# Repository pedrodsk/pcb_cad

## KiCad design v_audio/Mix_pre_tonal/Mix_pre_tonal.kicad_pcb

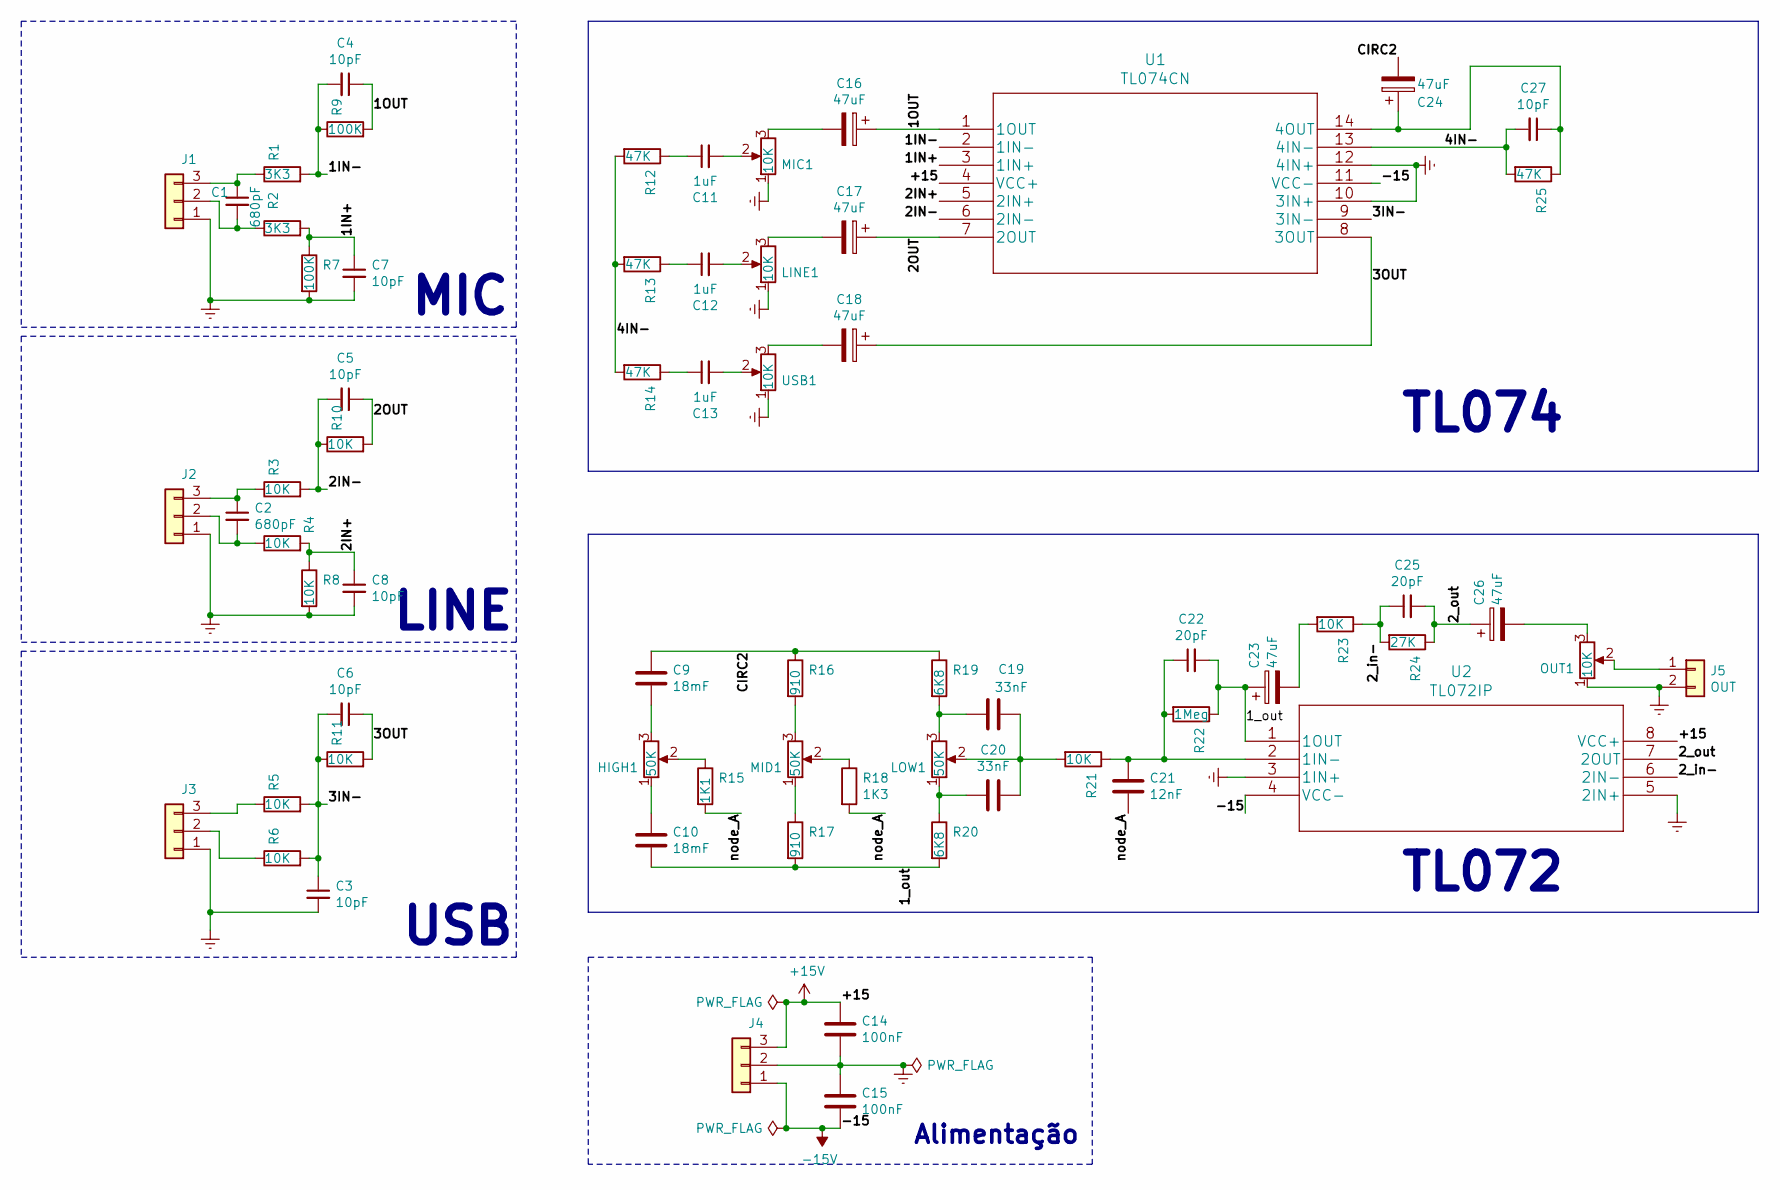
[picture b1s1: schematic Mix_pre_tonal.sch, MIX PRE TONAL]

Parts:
C1, C2: 680pF; C_Disc_D3.0mm_W1.6mm_P2.50mm
C3, C4, C5, C6, C7, C8, C27: 10pF; C_Disc_D3.0mm_W1.6mm_P2.50mm
C9, C10: 18mF; C_Disc_D7.0mm_W2.5mm_P5.00mm
C11, C12, C13: 1uF; C_Disc_D3.0mm_W1.6mm_P2.50mm
C14, C15: 100nF; C_Disc_D7.0mm_W2.5mm_P5.00mm
C16, C17, C18, C23, C24, C26: 47uF; CP_Radial_D4.0mm_P1.50mm
C19, C20: 33nF; C_Disc_D7.0mm_W2.5mm_P5.00mm
C21: 12nF; C_Disc_D7.0mm_W2.5mm_P5.00mm
C22, C25: 20pF; C_Disc_D3.0mm_W1.6mm_P2.50mm
HIGH1: 50K; Pot
J1: MIC; JST_NV_B03P-NV_1x03_P5.00mm_Vertical
J2: LINE; JST_NV_B03P-NV_1x03_P5.00mm_Vertical
J3: USB; JST_NV_B03P-NV_1x03_P5.00mm_Vertical
J4: Alimentação; JST_NV_B03P-NV_1x03_P5.00mm_Vertical
J5: OUT; JST_NV_B02P-NV_1x02_P5.00mm_Vertical
LINE1: 10K; Pot
LOW1: 50K; Pot
MIC1: 10K; Pot
MID1: 50K; Pot
OUT1: 10K; Pot
R1, R2: 3K3; R_Axial_DIN0207_L6.3mm_D2.5mm_P7.62mm_Horizontal
R3, R4, R5, R6, R8, R10, R11, R21, R23: 10K; R_Axial_DIN0207_L6.3mm_D2.5mm_P7.62mm_Horizontal
R7, R9: 100K; R_Axial_DIN0207_L6.3mm_D2.5mm_P7.62mm_Horizontal
R12, R13, R14, R25: 47K; R_Axial_DIN0207_L6.3mm_D2.5mm_P7.62mm_Horizontal
R15: 1K1; R_Axial_DIN0207_L6.3mm_D2.5mm_P7.62mm_Horizontal
R16, R17: 910; R_Axial_DIN0207_L6.3mm_D2.5mm_P7.62mm_Horizontal
R18: 1K3; R_Axial_DIN0207_L6.3mm_D2.5mm_P7.62mm_Horizontal
R19, R20: 6K8; R_Axial_DIN0207_L6.3mm_D2.5mm_P7.62mm_Horizontal
R22: 1Meg; R_Axial_DIN0207_L6.3mm_D2.5mm_P7.62mm_Horizontal
R24: 27K; R_Axial_DIN0207_L6.3mm_D2.5mm_P7.62mm_Horizontal
U1: TL074CN
U2: TL072IP
USB1: 10K; Pot

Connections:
+15V: C14.1, J4.3, U1.4 (VCC+), U2.8 (VCC+)
-15V: C15.2, J4.1, U1.11 (VCC-), U2.4 (VCC-)
/1IN+: C7.1, R2.2, R7.1, U1.3 (1IN+)
/1IN-: C4.2, R1.2, R9.1, U1.2 (1IN-)
/1OUT: C4.1, C16.1, R9.2, U1.1 (1OUT)
/1_out: C10.2, C22.2, C23.1, R17.2, R20.2, R22.1, U2.1 (1OUT)
/2IN+: C8.1, R4.2, R8.1, U1.5 (2IN+)
/2IN-: C5.2, R3.2, R10.1, U1.6 (2IN-)
/2OUT: C5.1, C17.1, R10.2, U1.7 (2OUT)
/2_in-: C25.1, R23.1, R24.2, U2.6 (2IN-)
/2_out: C25.2, C26.1, R24.1, U2.7 (2OUT)
/3IN-: C3.1, C6.2, R5.2, R6.2, R11.1, U1.9 (3IN-)
/3OUT: C6.1, C18.1, R11.2, U1.8 (3OUT)
/4IN-: C27.2, R12.2, R13.2, R14.2, R25.2, U1.13 (4IN-)
/CIRC2: C9.1, C24.2, R16.1, R19.1
/node_A: C21.1, R15.2, R18.2
GNDREF: C3.2, C7.2, C8.2, C14.2, C15.1, J1.1, J2.1, J3.1, J4.2, J5.2, LINE1.1, MIC1.1, OUT1.1, R7.2, R8.2, U1.10 (3IN+), U1.12 (4IN+), U2.3 (1IN+), U2.5 (2IN+), USB1.1
unnamed: C1.1, J1.3, R1.1
unnamed: C1.2, J1.2, R2.1
unnamed: C2.1, J2.3, R3.1
unnamed: C2.2, J2.2, R4.1
unnamed: C9.2, HIGH1.3
unnamed: C10.1, HIGH1.1
unnamed: C11.1, R12.1
unnamed: C11.2, MIC1.2
unnamed: C12.1, R13.1
unnamed: C12.2, LINE1.2
unnamed: C13.1, R14.1
unnamed: C13.2, USB1.2
unnamed: C16.2, MIC1.3
unnamed: C17.2, LINE1.3
unnamed: C18.2, USB1.3
unnamed: C19.1, C20.1, LOW1.2, R21.2
unnamed: C19.2, LOW1.3, R19.2
unnamed: C20.2, LOW1.1, R20.1
unnamed: C21.2, C22.1, R21.1, R22.2, U2.2 (1IN-)
unnamed: C23.2, R23.2
unnamed: C24.1, C27.1, R25.1, U1.14 (4OUT)
unnamed: C26.2, OUT1.3
unnamed: HIGH1.2, R15.1
unnamed: J3.2, R6.1
unnamed: J3.3, R5.1
unnamed: J5.1, OUT1.2
unnamed: MID1.1, R17.1
unnamed: MID1.2, R18.1
unnamed: MID1.3, R16.2

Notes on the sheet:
MIC
LINE
USB
TL074
TL072
Alimentação

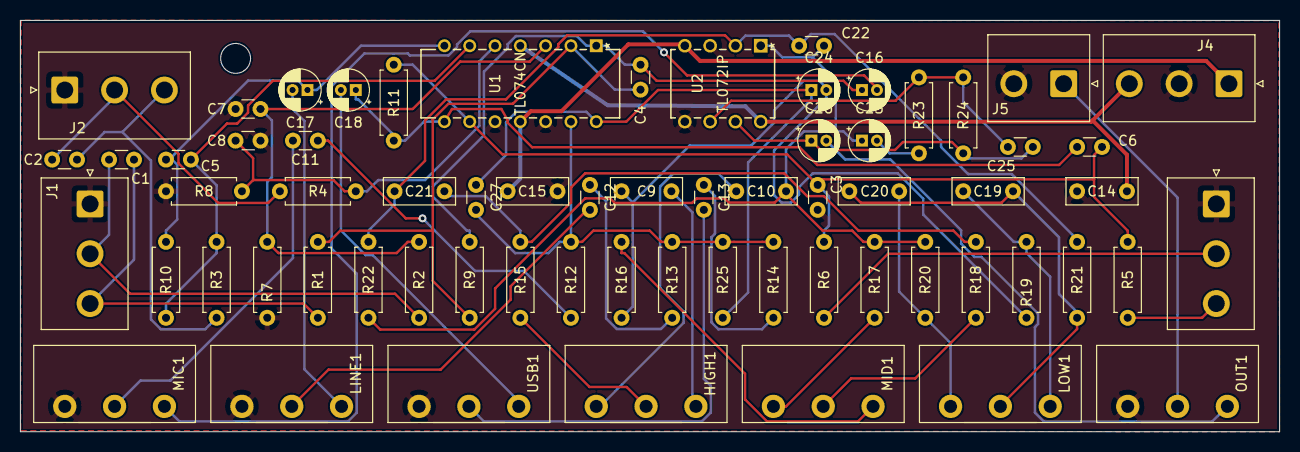
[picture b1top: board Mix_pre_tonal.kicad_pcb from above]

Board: 2 copper layers, 126.4 x 41.3 mm, 66 parts (0 on the bottom side), 46 nets.

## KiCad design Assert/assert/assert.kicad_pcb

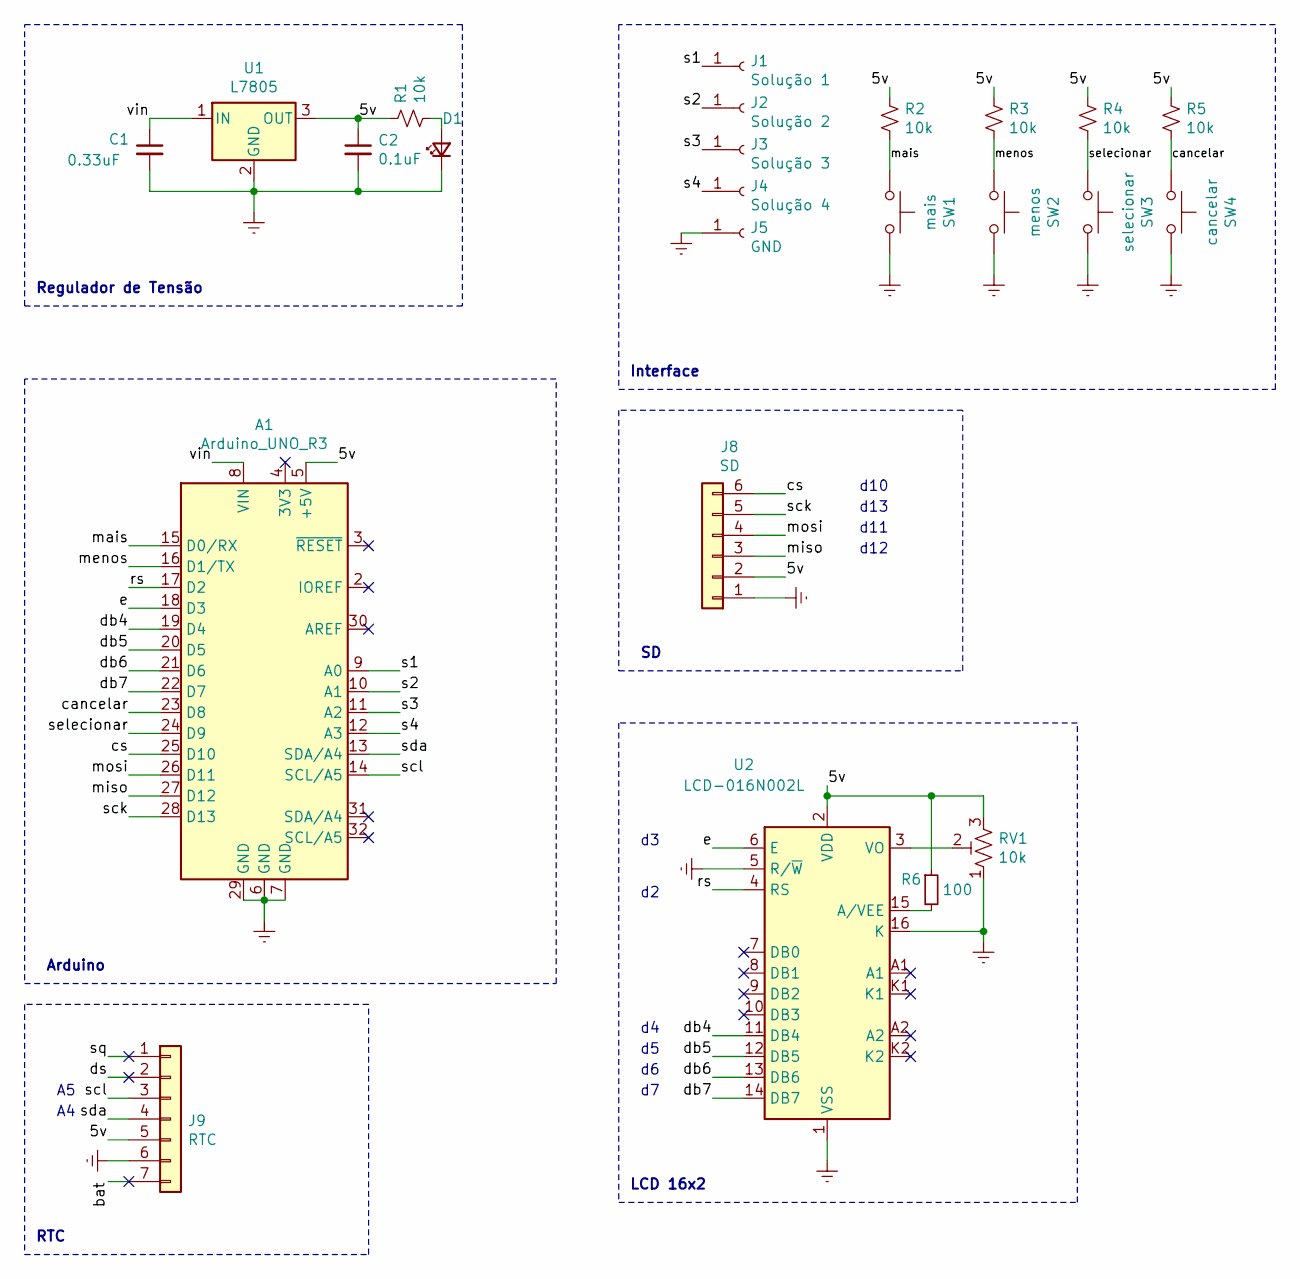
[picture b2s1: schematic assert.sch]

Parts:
A1: Arduino_UNO_R3
C1: 0.33uF; C_Disc_D3.0mm_W1.6mm_P2.50mm
C2: 0.1uF; C_Disc_D3.0mm_W1.6mm_P2.50mm
D1: LED_Small; LED_D3.0mm
J1: Solução 1; Banana_Jack_1Pin
J2: Solução 2; Banana_Jack_1Pin
J3: Solução 3; Banana_Jack_1Pin
J4: Solução 4; Banana_Jack_1Pin
J5: GND; Banana_Jack_1Pin
J8: SD; PinSocket_1x06_P2.54mm_Vertical
J9: RTC; PinSocket_1x07_P2.54mm_Vertical
R1, R2, R3, R4, R5: 10k; R_Axial_DIN0207_L6.3mm_D2.5mm_P7.62mm_Horizontal
R6: 100; R_Axial_DIN0207_L6.3mm_D2.5mm_P7.62mm_Horizontal
RV1: 10k; Potentiometer_Bourns_3386C_Horizontal
SW1: mais; SW_PUSH_6mm
SW2: menos; SW_PUSH_6mm
SW3: selecionar; SW_PUSH_6mm
SW4: cancelar; SW_PUSH_6mm
U1: L7805; TO-220-3_Horizontal_TabDown
U2: LCD-016N002L; WC1602A

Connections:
/5v: A1.5 (+5V), C2.1, J8.2, J9.5, R1.1, R2.1, R3.1, R4.1, R5.1, R6.1, RV1.3, U1.3 (OUT), U2.2 (VDD)
/bat: J9.7
/cancelar: A1.23 (D8), R5.2, SW4.1
/cs: A1.25 (D10), J8.6
/db4: A1.19 (D4), U2.11 (DB4)
/db5: A1.20 (D5), U2.12 (DB5)
/db6: A1.21 (D6), U2.13 (DB6)
/db7: A1.22 (D7), U2.14 (DB7)
/ds: J9.2
/e: A1.18 (D3), U2.6 (E)
/mais: A1.15 (D0/RX), R2.2, SW1.1
/menos: A1.16 (D1/TX), R3.2, SW2.1
/miso: A1.27 (D12), J8.3
/mosi: A1.26 (D11), J8.4
/rs: A1.17 (D2), U2.4 (RS)
/s1: A1.9 (A0), J1.1
/s2: A1.10 (A1), J2.1
/s3: A1.11 (A2), J3.1
/s4: A1.12 (A3), J4.1
/sck: A1.28 (D13), J8.5
/scl: A1.14 (SCL/A5), J9.3
/sda: A1.13 (SDA/A4), J9.4
/selecionar: A1.24 (D9), R4.2, SW3.1
/sq: J9.1
/vin: A1.8 (VIN), C1.1, U1.1 (IN)
GNDREF: A1.6 (GND), A1.7 (GND), A1.29 (GND), C1.2, C2.2, D1.1 (K), J5.1, J8.1, J9.6, RV1.1, SW1.2, SW2.2, SW3.2, SW4.2, U1.2 (GND), U2.1 (VSS), U2.5 (R/~W), U2.16 (K)
unnamed: D1.2 (A), R1.2
unnamed: R6.2, U2.15 (A/VEE)
unnamed: RV1.2, U2.3 (VO)

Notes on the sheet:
Regulador de Tensão
LCD 16x2
d12
d11
d13
d10
Interface
RTC
Arduino

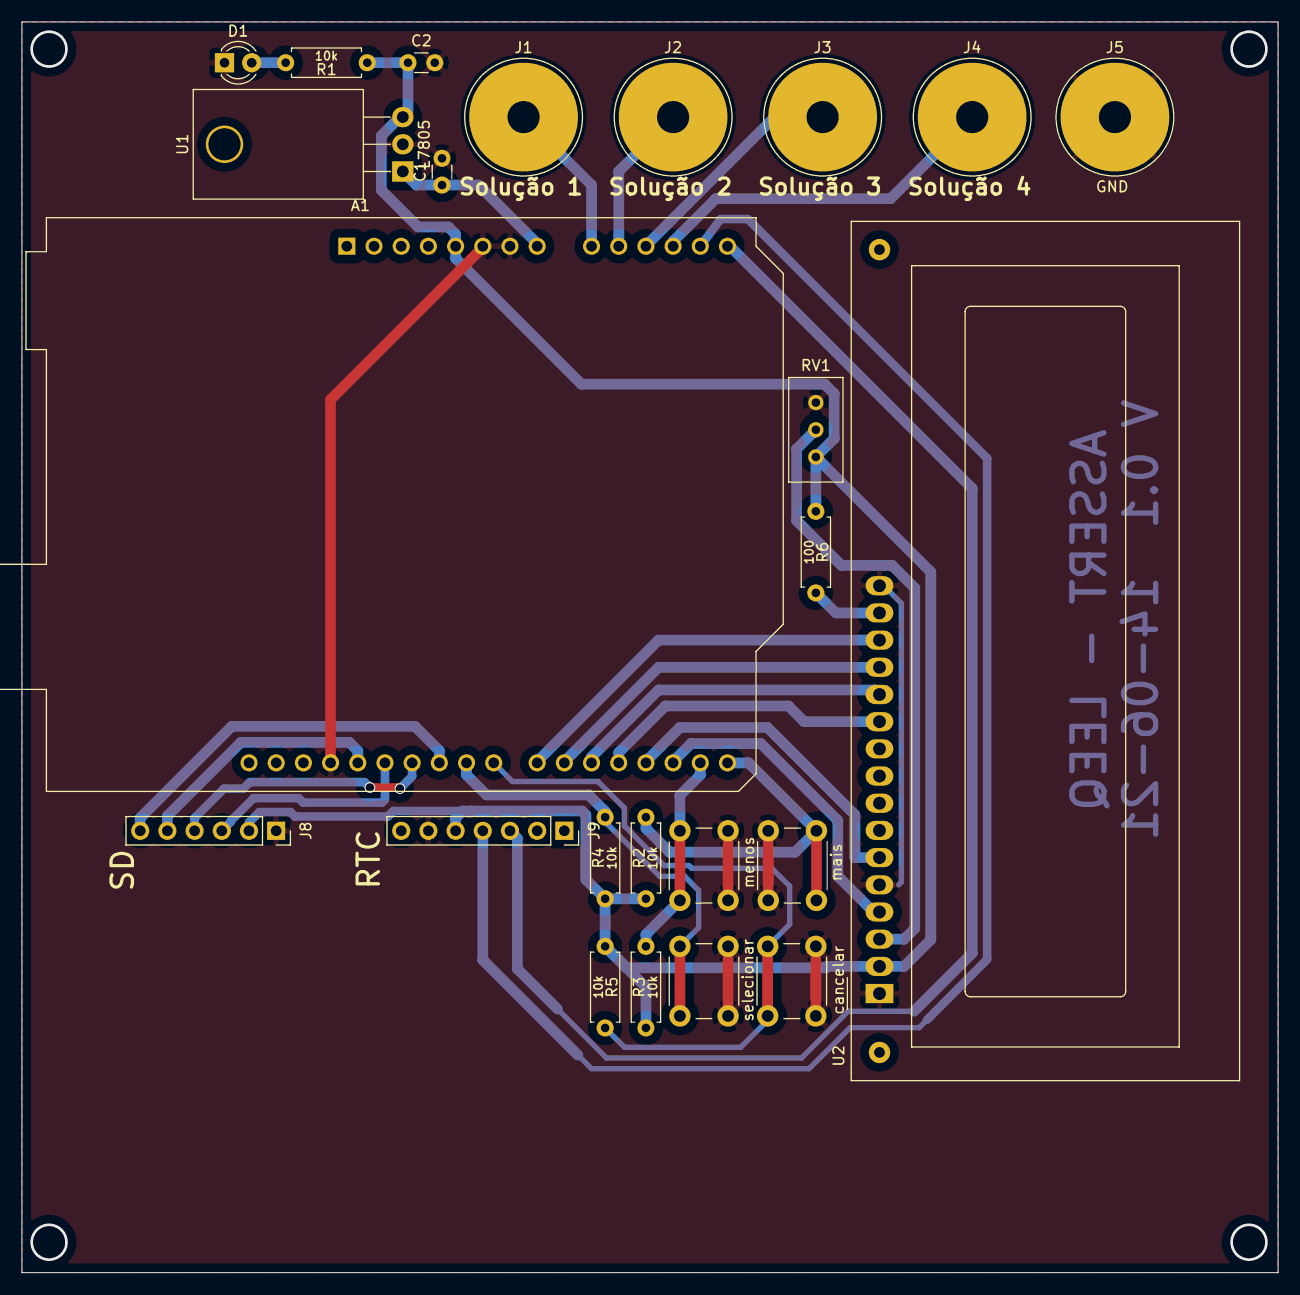
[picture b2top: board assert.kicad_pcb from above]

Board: 2 copper layers, 117.3 x 116.8 mm, 24 parts (0 on the bottom side), 26 nets.

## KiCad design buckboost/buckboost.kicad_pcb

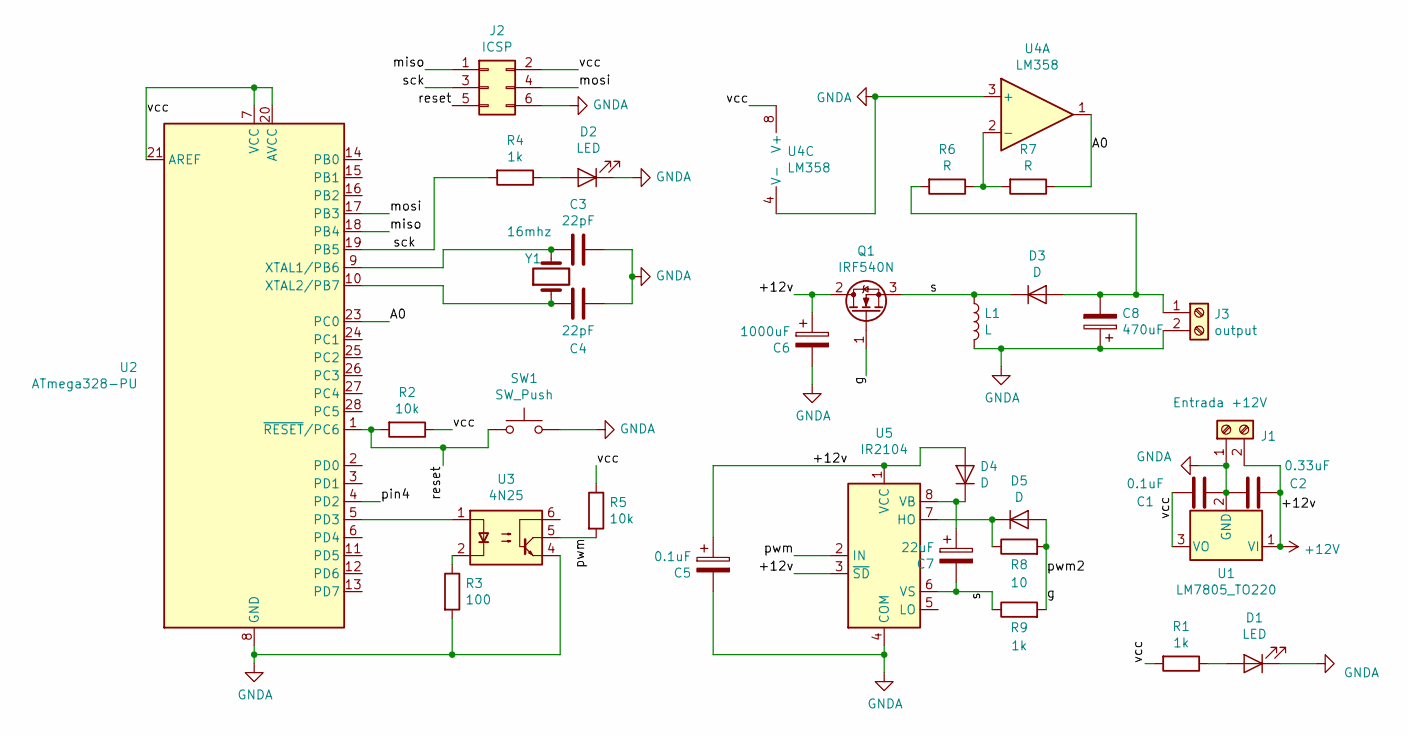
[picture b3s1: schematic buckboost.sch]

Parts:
C1: 0.1uF; C_Disc_D3.0mm_W1.6mm_P2.50mm
C2: 0.33uF; C_Disc_D3.0mm_W1.6mm_P2.50mm
C3, C4: 22pF; C_Disc_D3.0mm_W1.6mm_P2.50mm
C5: 0.1uF; CP_Radial_D5.0mm_P2.50mm
C6: 1000uF; CP_Radial_D5.0mm_P2.50mm
C7: 22uF; CP_Radial_D5.0mm_P2.50mm
C8: 470uF; CP_Radial_D12.5mm_P5.00mm
D1, D2: LED; LED_D3.0mm
D3: D; D_P600_R-6_P20.00mm_Horizontal
D4, D5: D; D_A-405_P7.62mm_Horizontal
J1: Entrada +12V; TerminalBlock_bornier-2_P5.08mm
J2: ICSP; IDC-Header_2x03_P2.54mm_Vertical
J3: output; TerminalBlock_bornier-2_P5.08mm
L1: L; L_Toroid_Horizontal_D12.7mm_P20.00mm_Diameter14-5mm_Amidon-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
Q1: IRF540N; TO-220-3_Vertical
R1, R4, R9: 1k; R_Axial_DIN0204_L3.6mm_D1.6mm_P5.08mm_Horizontal
R2, R5: 10k; R_Axial_DIN0204_L3.6mm_D1.6mm_P5.08mm_Horizontal
R3: 100; R_Axial_DIN0204_L3.6mm_D1.6mm_P5.08mm_Horizontal
R6, R7: R; R_Axial_DIN0204_L3.6mm_D1.6mm_P5.08mm_Horizontal
R8: 10; R_Axial_DIN0204_L3.6mm_D1.6mm_P5.08mm_Horizontal
SW1: SW_Push; SW_PUSH_6mm_H4.3mm
U1: LM7805_TO220; TO-220-3_Vertical
U2: ATmega328-PU; DIP-28_W7.62mm
U3: 4N25; DIP-6_W7.62mm
U4: LM358; DIP-8_W7.62mm_LongPads
U5: IR2104; DIP-8_W7.62mm_LongPads
Y1: 16mhz; Crystal_HC18-U_Vertical

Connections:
+12V: C2.2, C5.1, C6.1, D4.2 (A), J1.2, Q1.2 (D), U1.1 (VI), U5.1 (VCC), U5.3 (~SD)
/A0: R7.1, U2.23 (PC0), U4.1
/g: D5.2 (A), Q1.1 (G), R8.2, R9.2
/miso: J2.1, U2.18 (PB4)
/mosi: J2.4, U2.17 (PB3)
/pin4: U2.4 (PD2)
/pwm: R5.2, U3.5, U5.2 (IN)
/reset: J2.5, R2.2, SW1.1, U2.1 (~RESET~/PC6)
/s: C7.2, D3.1 (K), L1.1, Q1.3 (S), R9.1, U5.6 (VS)
/sck: J2.3, R4.2, U2.19 (PB5)
/vcc: C1.1, J2.2, R1.2, R2.1, R5.1, U1.3 (VO), U2.7 (VCC), U2.20 (AVCC), U2.21 (AREF), U4.8 (V+)
GNDA: C1.2, C2.1, C3.1, C4.2, C5.2, C6.2, C8.1, D1.1 (K), D2.1 (K), J1.1, J2.6, J3.2, L1.2, R3.2, SW1.2, U1.2 (GND), U2.8 (GND), U2.22 (GND), U3.4, U4.3 (+), U4.4 (V-), U5.4 (COM)
unnamed: C3.2, U2.9 (XTAL1/PB6), Y1.2
unnamed: C4.1, U2.10 (XTAL2/PB7), Y1.1
unnamed: C7.1, D4.1 (K), U5.8 (VB)
unnamed: C8.2, D3.2 (A), J3.1, R6.2
unnamed: D1.2 (A), R1.1
unnamed: D2.2 (A), R4.1
unnamed: D5.1 (K), R8.1, U5.7 (HO)
unnamed: R3.1, U3.2
unnamed: R6.1, R7.2, U4.2 (-)
unnamed: U2.5 (PD3), U3.1

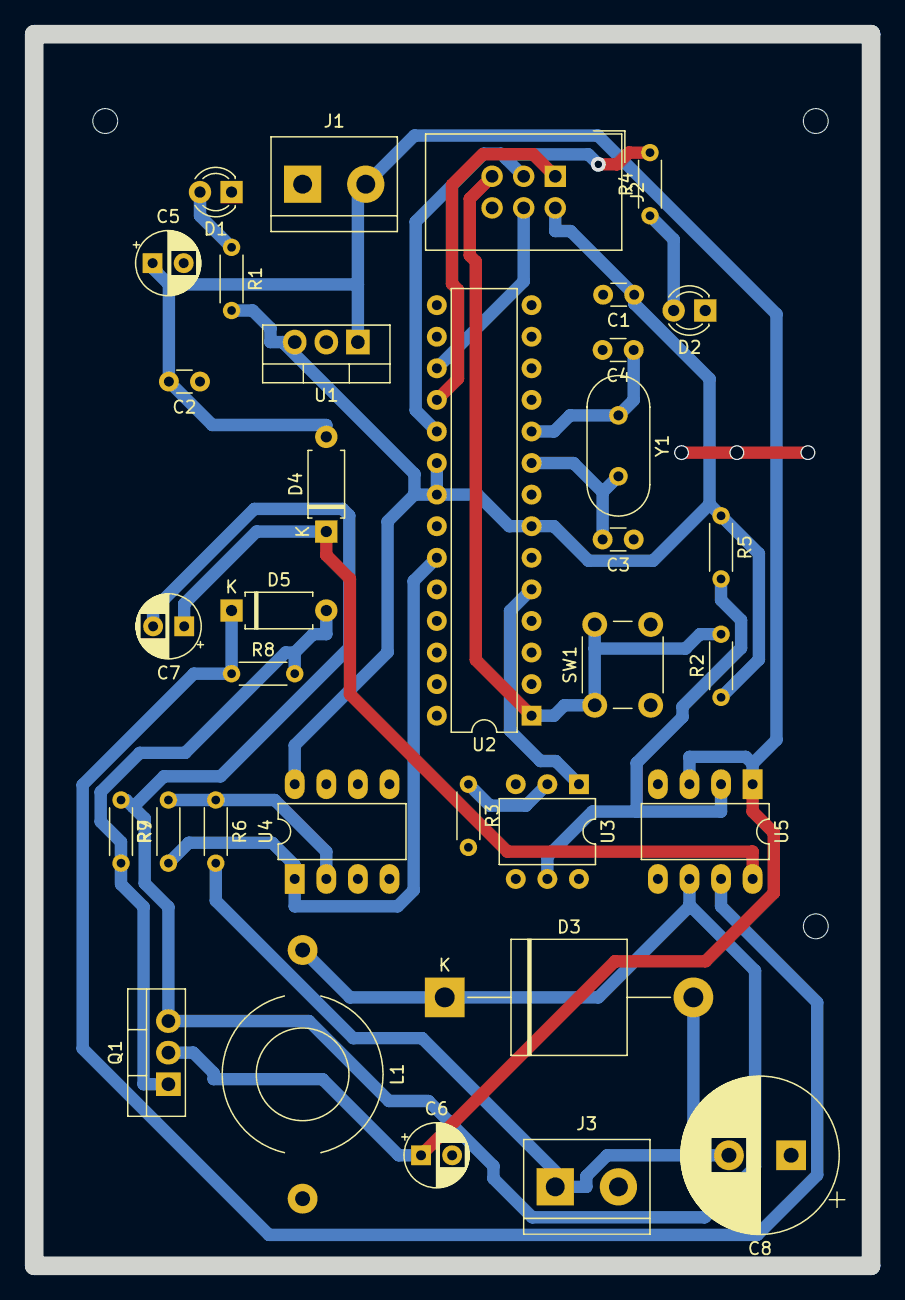
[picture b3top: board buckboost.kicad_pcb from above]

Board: 2 copper layers, 67.3 x 99.1 mm, 34 parts (0 on the bottom side), 21 nets.

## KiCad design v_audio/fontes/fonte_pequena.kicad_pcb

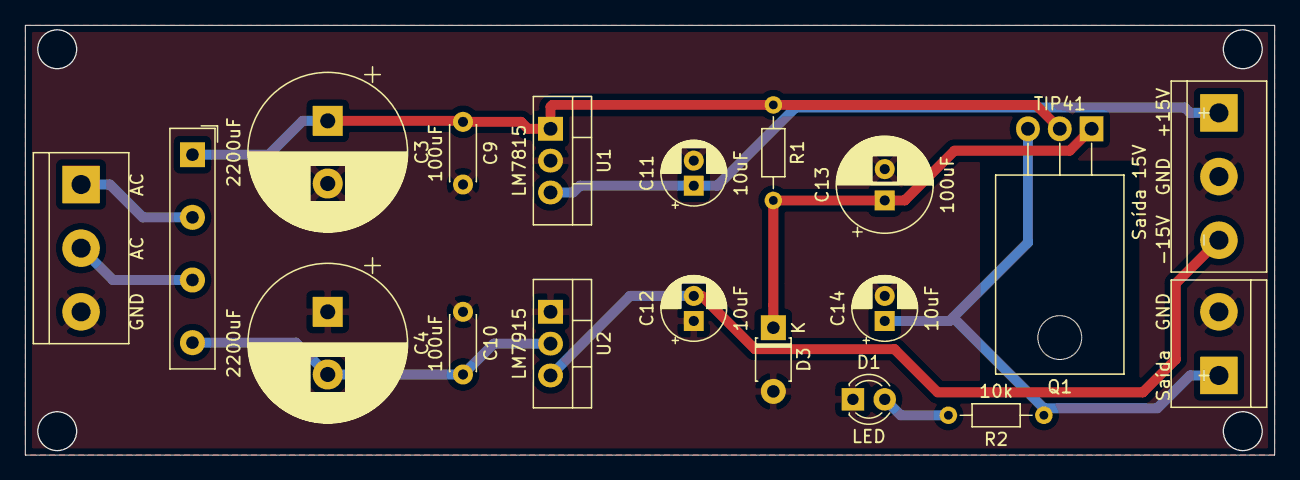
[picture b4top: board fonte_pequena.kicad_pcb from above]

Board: 2 copper layers, 99.7 x 34.3 mm, 19 parts (0 on the bottom side), 10 nets.

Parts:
C3, C4: 2200uF; CP_Radial_D12.5mm_P5.00mm
C9, C10: 100uF; C_Disc_D4.3mm_W1.9mm_P5.00mm
C11, C12, C14: 10uF; CP_Radial_D5.0mm_P2.00mm
C13: 100uF; CP_Radial_D7.5mm_P2.50mm
D1: LED; LED_D3.0mm
D2: D_Bridge_+-AA; Diode_Bridge_19.0x3.5x10.0mm_P5.0mm
D3: 1n4442; D_T-1_P5.08mm_Horizontal
Entrada1: Screw_Terminal_01x03; TerminalBlock_bornier-3_P5.08mm
Q1: TIP41; TO-220-3_Horizontal_TabDown
R1: R; R_Axial_DIN0204_L3.6mm_D1.6mm_P7.62mm_Horizontal
R2: 10k; R_Axial_DIN0204_L3.6mm_D1.6mm_P7.62mm_Horizontal
Saída: Screw_Terminal_01x02; TerminalBlock_bornier-2_P5.08mm
Saída 15V: Conn_01x03_Male; TerminalBlock_bornier-3_P5.08mm
U1: LM7815; TO-220-3_Vertical
U2: LM7915; TO-220-3_Vertical

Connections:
/AC2: D2.3, Entrada1.2
GNDA: C3.2, C4.1, C9.2, C10.1, C11.2, C12.1, C13.2, C14.2, D1.1, D3.2, Entrada1.3, Saída.2, Saída 15V.2, U1.2, U2.1
unnamed: C3.1, C9.1, D2.1, Q1.2, R1.1, U1.1
unnamed: C4.2, C10.2, D2.4, U2.2
unnamed: C11.1, Saída 15V.1, U1.3
unnamed: C12.2, Saída 15V.3, U2.3
unnamed: C13.1, D3.1, Q1.1, R1.2
unnamed: C14.1, Q1.3, R2.1, Saída.1
unnamed: D1.2, R2.2
unnamed: D2.2, Entrada1.1

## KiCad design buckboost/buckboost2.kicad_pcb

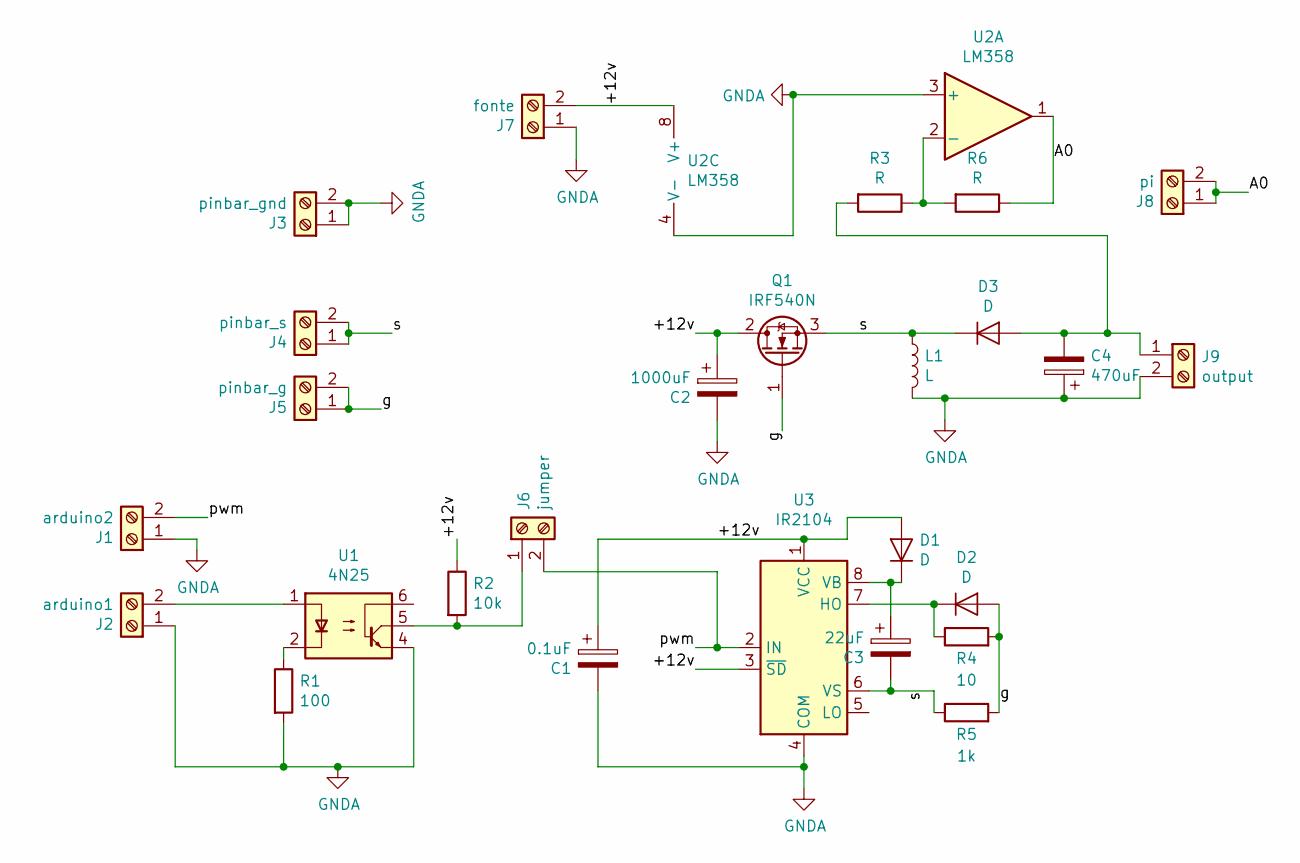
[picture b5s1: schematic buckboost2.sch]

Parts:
C1: 0.1uF; CP_Radial_D5.0mm_P2.50mm
C2: 1000uF; CP_Radial_D5.0mm_P2.50mm
C3: 22uF; CP_Radial_D5.0mm_P2.50mm
C4: 470uF; CP_Radial_D12.5mm_P5.00mm
D1, D2: D; D_A-405_P7.62mm_Horizontal
D3: D; D_P600_R-6_P20.00mm_Horizontal
J1: arduino2; TerminalBlock_bornier-2_P5.08mm
J2: arduino1; TerminalBlock_bornier-2_P5.08mm
J3: pinbar_gnd; TerminalBlock_bornier-2_P5.08mm
J4: pinbar_s; TerminalBlock_bornier-2_P5.08mm
J5: pinbar_g; TerminalBlock_bornier-2_P5.08mm
J6: jumper; TerminalBlock_bornier-2_P5.08mm
J7: fonte; TerminalBlock_bornier-2_P5.08mm
J8: pi; TerminalBlock_bornier-2_P5.08mm
J9: output; TerminalBlock_bornier-2_P5.08mm
L1: L; L_Toroid_Horizontal_D12.7mm_P20.00mm_Diameter14-5mm_Amidon-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
Q1: IRF540N; TO-220-3_Vertical
R1: 100; R_Axial_DIN0204_L3.6mm_D1.6mm_P7.62mm_Horizontal
R2: 10k; R_Axial_DIN0204_L3.6mm_D1.6mm_P5.08mm_Horizontal
R3, R6: R; R_Axial_DIN0204_L3.6mm_D1.6mm_P5.08mm_Horizontal
R4: 10; R_Axial_DIN0204_L3.6mm_D1.6mm_P5.08mm_Horizontal
R5: 1k; R_Axial_DIN0204_L3.6mm_D1.6mm_P5.08mm_Horizontal
U1: 4N25; DIP-6_W7.62mm
U2: LM358; DIP-8_W7.62mm_LongPads
U3: IR2104; DIP-8_W7.62mm_LongPads

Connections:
/+12v: C1.1, C2.1, D1.2 (A), J7.2, Q1.2 (D), R2.1, U2.8 (V+), U3.1 (VCC), U3.3 (~SD)
/A0: J8.1, J8.2, R6.1, U2.1
/g: D2.2 (A), J5.1, J5.2, Q1.1 (G), R4.2, R5.2
/pwm: J1.2, J6.2, U3.2 (IN)
/s: C3.2, D3.1 (K), J4.1, J4.2, L1.1, Q1.3 (S), R5.1, U3.6 (VS)
GNDA: C1.2, C2.2, C4.1, J1.1, J2.1, J3.1, J3.2, J7.1, J9.2, L1.2, R1.2, U1.4, U2.3 (+), U2.4 (V-), U3.4 (COM)
unnamed: C3.1, D1.1 (K), U3.8 (VB)
unnamed: C4.2, D3.2 (A), J9.1, R3.2
unnamed: D2.1 (K), R4.1, U3.7 (HO)
unnamed: J2.2, U1.1
unnamed: J6.1, R2.2, U1.5
unnamed: R1.1, U1.2
unnamed: R3.1, R6.2, U2.2 (-)

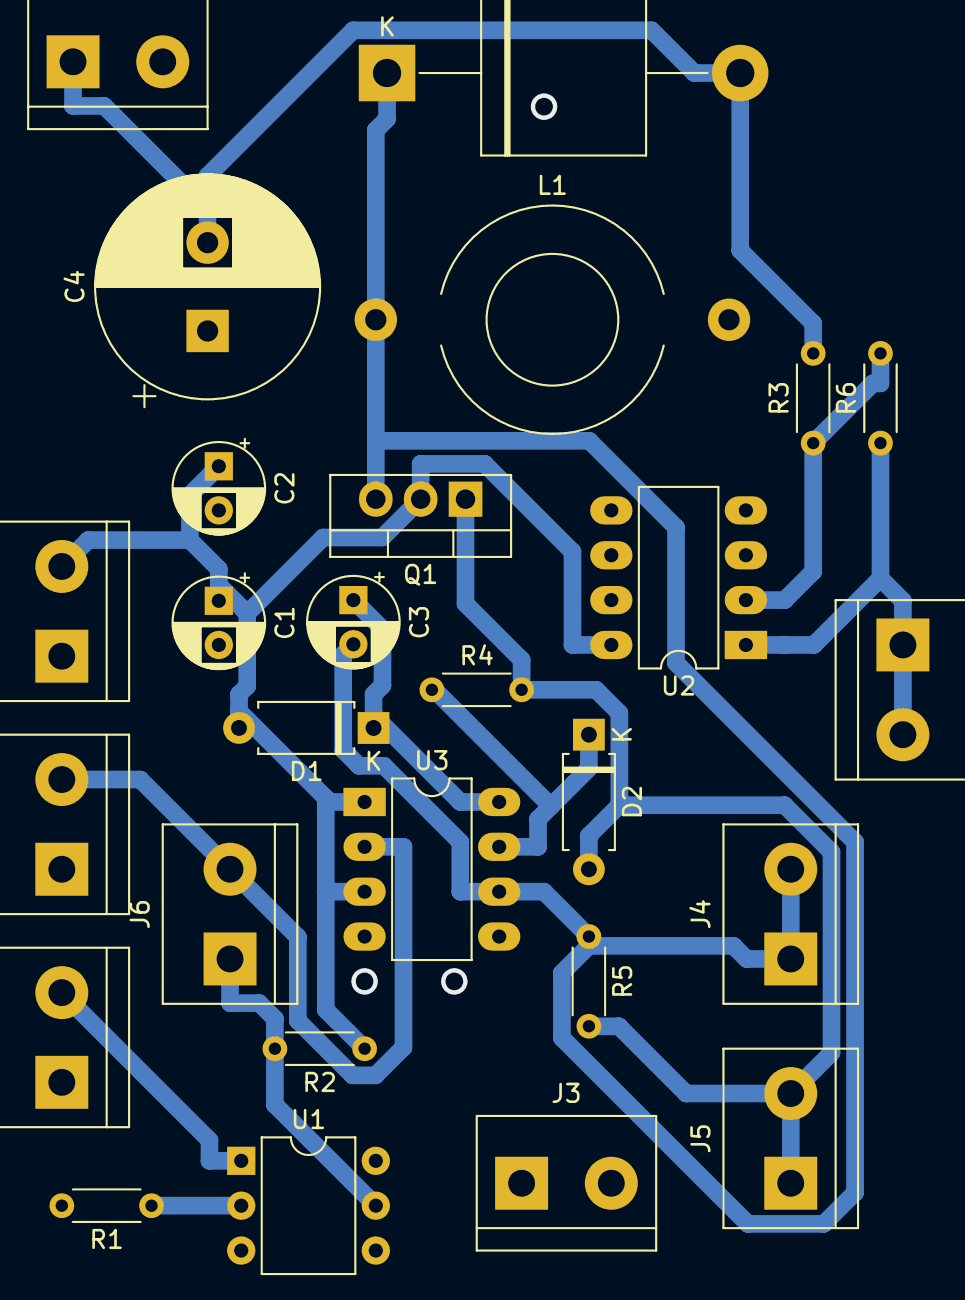
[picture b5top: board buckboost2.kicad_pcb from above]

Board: 2 copper layers, 27 parts (0 on the bottom side), 13 nets.

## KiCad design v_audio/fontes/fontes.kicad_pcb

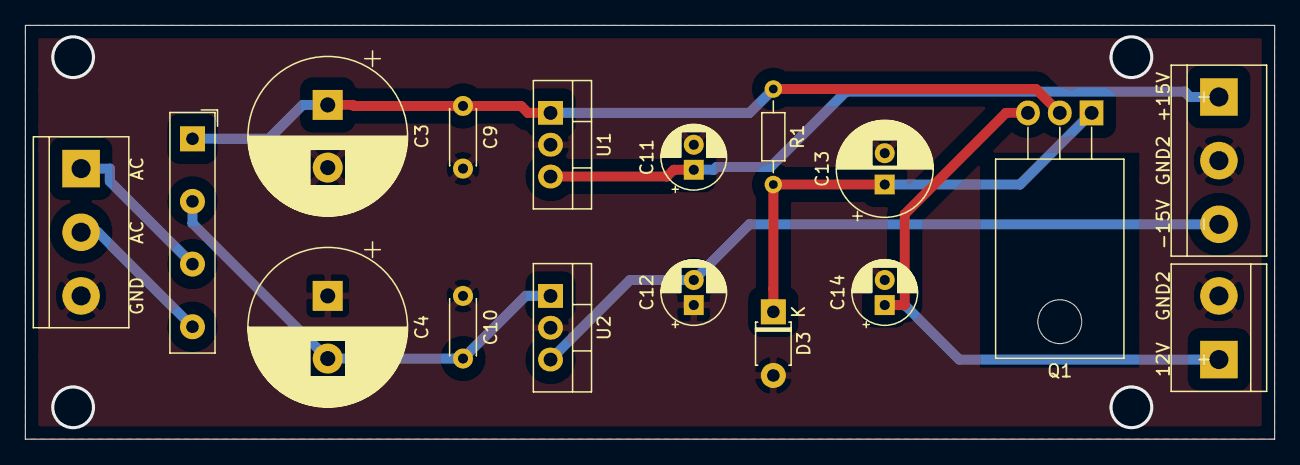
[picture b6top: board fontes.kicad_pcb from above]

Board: 2 copper layers, 99.7 x 33.0 mm, 17 parts (0 on the bottom side), 9 nets.

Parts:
12V: Screw_Terminal_01x02; TerminalBlock_bornier-2_P5.08mm
+15V: Conn_01x03_Male; TerminalBlock_bornier-3_P5.08mm
C3, C4: 2200uF; CP_Radial_D12.5mm_P5.00mm
C9, C10: 100uF; C_Disc_D4.3mm_W1.9mm_P5.00mm
C11, C12, C14: 10uF; CP_Radial_D5.0mm_P2.00mm
C13: 100uF; CP_Radial_D7.5mm_P2.50mm
D2: D_Bridge_+-AA; Diode_Bridge_19.0x3.5x10.0mm_P5.0mm
D3: 1n4442; D_T-1_P5.08mm_Horizontal
Entrada1: Screw_Terminal_01x03; TerminalBlock_bornier-3_P5.08mm
Q1: TIP41; TO-220-3_Horizontal_TabDown
R1: R; R_Axial_DIN0204_L3.6mm_D1.6mm_P7.62mm_Horizontal
U1, U2: LM7815_TO220; TO-220-3_Vertical

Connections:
/AC2: D2.4, Entrada1.2
GNDA: 12V.2, +15V.2, C3.2, C4.1, C9.2, C10.1, C11.2, C12.1, C13.2, C14.2, D3.2, Entrada1.3, U1.2, U2.2
unnamed: C3.1, C9.1, D2.1, Q1.2, R1.1, U1.1
unnamed: C4.2, C10.2, D2.2, U2.1
unnamed: +15V.1, C11.1, U1.3
unnamed: +15V.3, C12.2, U2.3
unnamed: C13.1, D3.1, Q1.1, R1.2
unnamed: 12V.1, C14.1, Q1.3
unnamed: D2.3, Entrada1.1

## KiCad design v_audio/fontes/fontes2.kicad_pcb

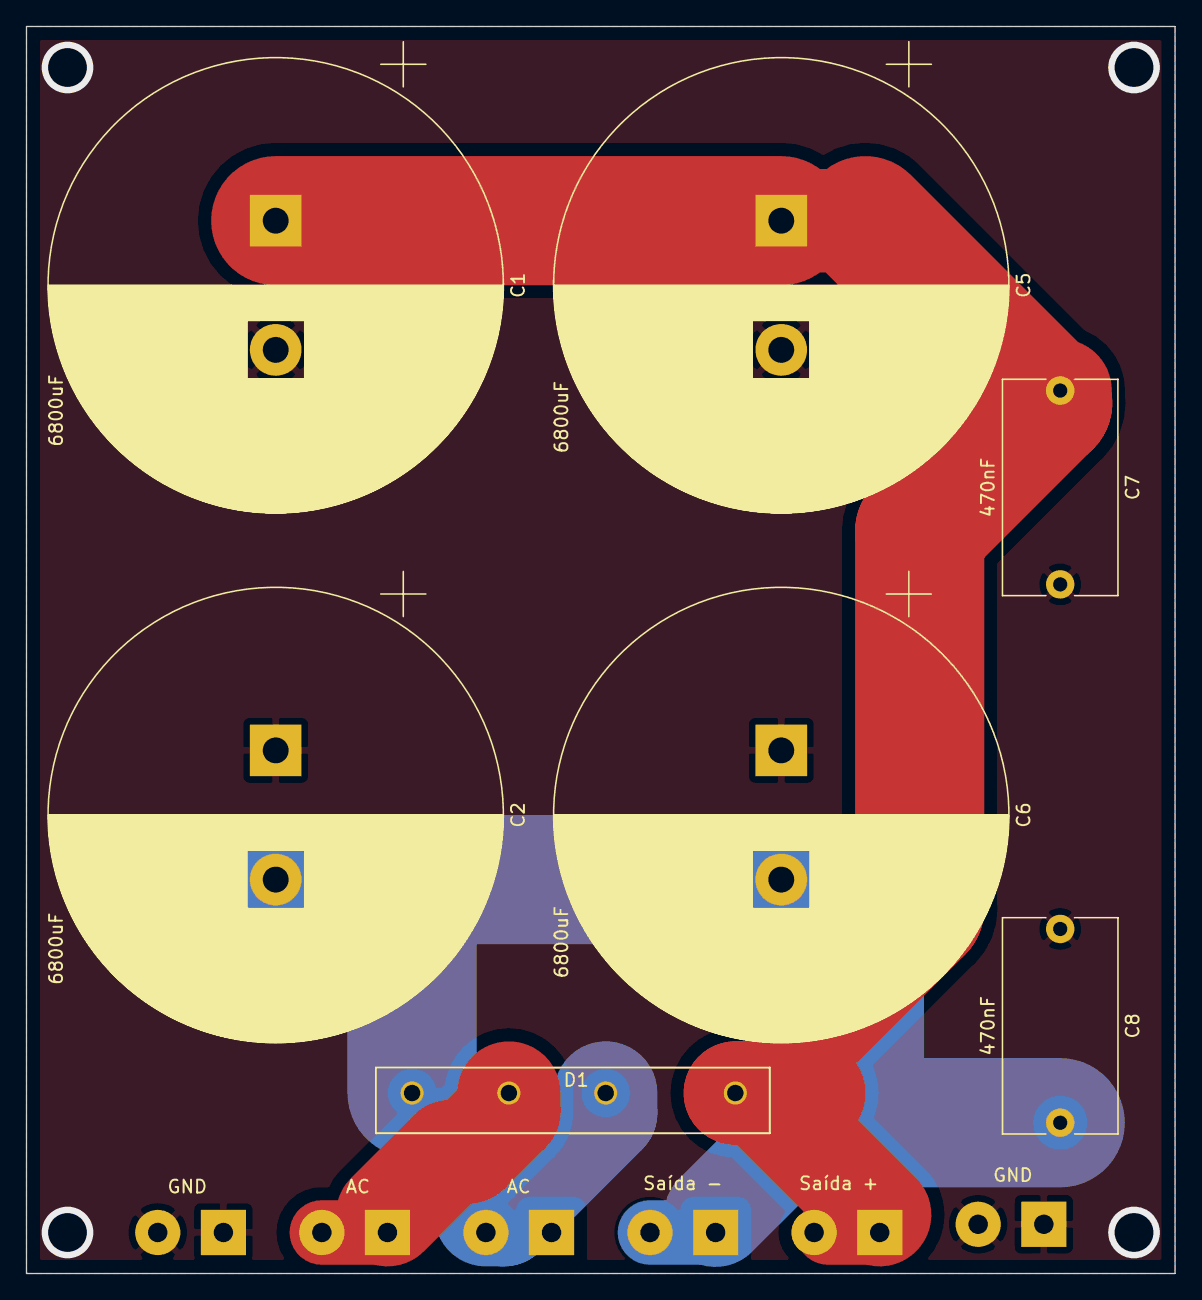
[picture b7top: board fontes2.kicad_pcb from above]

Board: 2 copper layers, 88.9 x 96.5 mm, 13 parts (0 on the bottom side), 5 nets.

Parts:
AC: Conn_Coaxial; SolderWirePad_1x02_P5.08mm_Drill1.5mm
AC#2: Conn_Coaxial; SolderWirePad_1x02_P5.08mm_Drill1.5mm
C1, C2, C5, C6: 6800uF; CP_Radial_D35.0mm_P10.00mm_SnapIn
C7, C8: 470nF; C_Rect_L16.5mm_W8.7mm_P15.00mm_MKT
D1: D_Bridge_+-AA; GBJ3510-BP
GND: Conn_Coaxial; SolderWirePad_1x02_P5.08mm_Drill1.5mm
GND#2: Conn_Coaxial; SolderWirePad_1x02_P5.08mm_Drill1.5mm
Saída +: Conn_Coaxial; SolderWirePad_1x02_P5.08mm_Drill1.5mm
Saída -: Conn_Coaxial; SolderWirePad_1x02_P5.08mm_Drill1.5mm

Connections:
/AC1: AC.1, AC.2, D1.2
GND: C1.2, C2.1, C5.2, C6.1, C7.2, C8.1, GND.1, GND.2, GND#2.1, GND#2.2
unnamed: AC#2.1, AC#2.2, D1.3
unnamed: C1.1, C5.1, C7.1, D1.1, Saída +.1, Saída +.2
unnamed: C2.2, C6.2, C8.2, D1.4, Saída -.1, Saída -.2
